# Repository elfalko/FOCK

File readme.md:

# FOCK - Falk's Overstaggered Corne Keyboard

FOCK at work, still waiting for batteries

Underside with simple standoff tenting and battery held by double sided tape

## Status

V2 is my daily driver running on ZMK since 09/22.

There is no firmware supporting the USB-C connection between halves yet, but electronically the connections should be sound.

## Why

[CRKBD](https://github.com/foostan/crkbd) is nice, but could use more stagger, a num row and USB-C

## Features

* fully reversible PCB
* 54 keys (6x4 + 4 thumb keys per side)
* nice!nanoV2 driven, pro-micro compatible
* usb c cable for connection between halves
* battery support
* [ZMK support](https://github.com/elfalko/fock-zmk)

Explicitly not planned:

* LEDs (over/under/any glow)
* return to TRRS
* Rotary encoders

## Repo overview

* Readme - this readme
* fock.yaml - generator file for [ergogen](https://github.com/ergogen/ergogen) (requires [the master branch from my fork](https://github.com/elfalko/ergogen/tree/master) though, since several footprints have been heavily updated)
* img/ - images for documentation
* [Assembly manual](./assembly.md)

## TODO or future plans

* [ ] QMK support
* [ ] optional num row w mouse bites
* [ ] good case
* [ ] trackball/trackpad support

## License and usage

Feel free to use anything in this repo for inspiration and for any projects.
If you do, please send me a message, I will be stoked to hear about it.

Officially, this is under LGPLv2.1 license.

Please be aware that this is a personal project and not subject to any kind of safety testing other than me using it daily and not having electrified myself doing so (yet).
All risks using this are your own.

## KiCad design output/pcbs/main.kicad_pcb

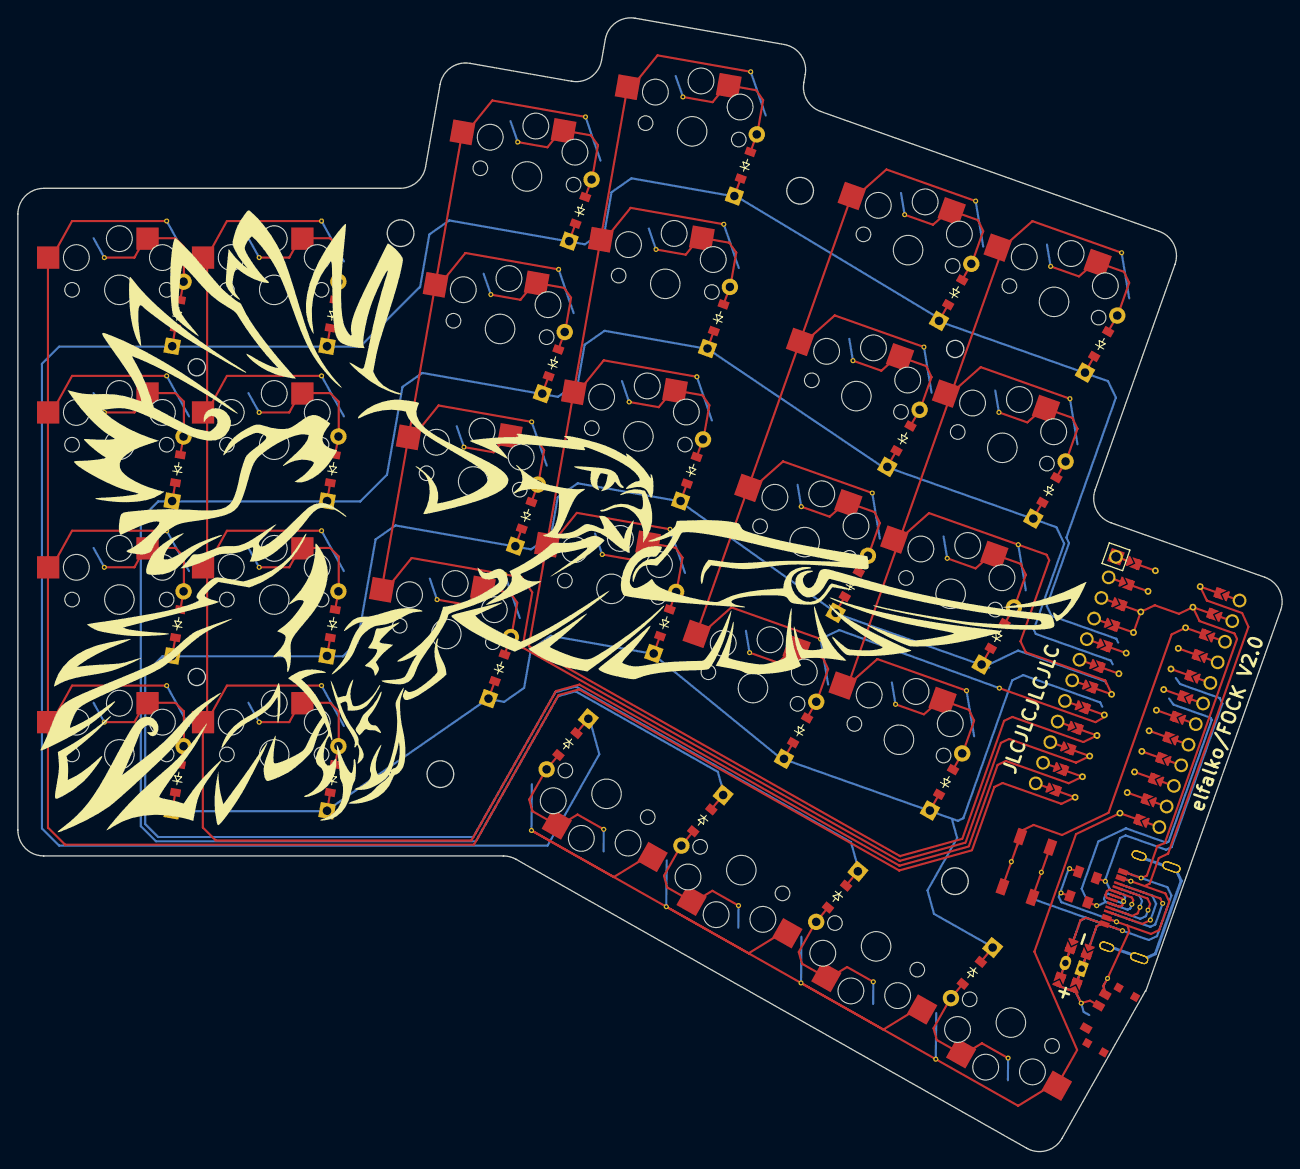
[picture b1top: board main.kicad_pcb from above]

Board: 2 copper layers, 147.0 x 131.8 mm, 71 parts (1 on the bottom side), 52 nets.

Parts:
B1: SW_TACT_ALPS_SKQGABE010
D1, D2, D3, D4, D5, D6, D7, D8, D9, D10, D11, D12, D13, D14, D15, D16, D17, D18, D19, D20, D21, D22, D23, D24, D25, D26, D27, D28: ComboDiode
J1, J2, J3, J4: solderjumper
JST1: JST_PH_S2B-PH-K_02x2.00mm_Angled
MCU1: ProMicro
PAD3, PAD4, PAD5, PAD6: SMDPad
S1, S2, S3, S4, S5, S6, S7, S8, S9, S10, S11, S12, S13, S14, S15, S16, S17, S18, S19, S20, S21, S22, S23, S24, S25, S26, S27, S28: PG1350
T1, T2: SPDT_C128955
USB1, USB2: USB-C-12-Pin-MidMount

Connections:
B1: J1.2, J3.2, JST1.1
B2: J2.2, J4.2, JST1.2
CC1: USB1.B5, USB2.B5
CC2: USB1.A5, USB2.A5
GND: B1.2, J3.1, J4.1, MCU1.2, MCU1.21, MCU1.22, USB1.A1, USB2.A1
P2: MCU1.20, USB1.A7, USB1.B7, USB2.A7, USB2.B7
P3: MCU1.19, USB1.A6, USB1.B6, USB2.A6, USB2.B6
P4: MCU1.18, S21.2, S22.2, S23.2, S24.2
P5: MCU1.17, S17.2, S18.2, S19.2, S20.2
P6: MCU1.16, PAD6.1, S13.2, S14.2, S15.2, S16.2
P7: MCU1.15, PAD5.1, S9.2, S10.2, S11.2, S12.2
P8: MCU1.14, PAD4.1, S5.2, S6.2, S7.2, S8.2
P9: MCU1.13, PAD3.1, S1.2, S2.2, S3.2, S4.2
P10: MCU1.12, S25.2, S26.2, S27.2, S28.2
P18: D1.1, D5.1, D9.1, D13.1, D17.1, D21.1, D25.1, MCU1.8
P19: D2.1, D6.1, D10.1, D14.1, D18.1, D22.1, D26.1, MCU1.7
P20: D3.1, D7.1, D11.1, D15.1, D19.1, D23.1, D27.1, MCU1.6
P21: D4.1, D8.1, D12.1, D16.1, D20.1, D24.1, D28.1, MCU1.5
RAW: MCU1.1, T1.3, T2.1, USB1.A4, USB2.A4
RAWER: J1.1, J2.1, T1.2, T2.2
RST: B1.1, MCU1.3
SBU1: USB1.A8, USB2.A8
SBU2: USB1.B8, USB2.B8
SHIELD: USB1.S1, USB2.S1
index_bottom: D17.2, S17.1
index_home: D18.2, S18.1
index_num: D20.2, S20.1
index_top: D19.2, S19.1
inner_bottom: D21.2, S21.1
inner_home: D22.2, S22.1
inner_num: D24.2, S24.1
inner_top: D23.2, S23.1
middle_bottom: D13.2, S13.1
middle_home: D14.2, S14.1
middle_num: D16.2, S16.1
middle_top: D15.2, S15.1
outer_bottom: D1.2, S1.1
outer_home: D2.2, S2.1
outer_num: D4.2, S4.1
outer_top: D3.2, S3.1
pinky_bottom: D5.2, S5.1
pinky_home: D6.2, S6.1
pinky_num: D8.2, S8.1
pinky_top: D7.2, S7.1
ring_bottom: D9.2, S9.1
ring_home: D10.2, S10.1
ring_num: D12.2, S12.1
ring_top: D11.2, S11.1
thumb_bottom: D25.2, S25.1
thumb_home: D26.2, S26.1
thumb_num: D28.2, S28.1
thumb_top: D27.2, S27.1

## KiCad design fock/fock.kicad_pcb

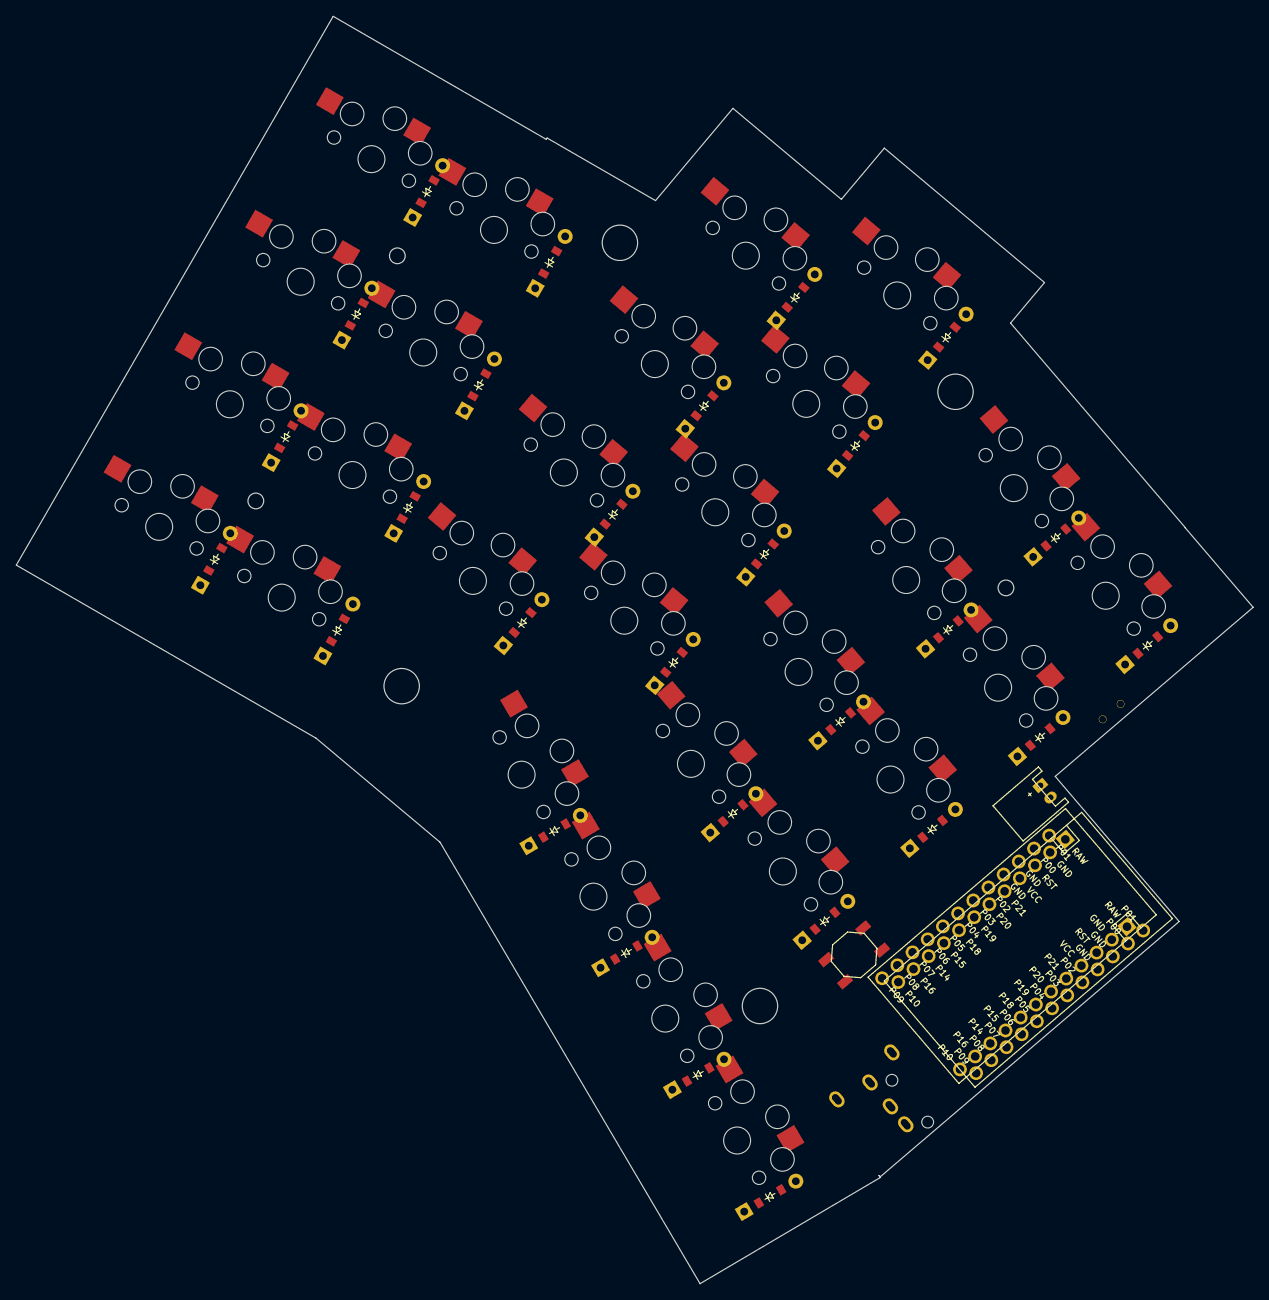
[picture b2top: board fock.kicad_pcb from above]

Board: 2 copper layers, 157.3 x 161.2 mm, 61 parts (0 on the bottom side), 54 nets, no tracks yet.

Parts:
B1: SW_TACT_ALPS_SKQGABE010
D1, D2, D3, D4, D5, D6, D7, D8, D9, D10, D11, D12, D13, D14, D15, D16, D17, D18, D19, D20, D21, D22, D23, D24, D25, D26, D27, D28: ComboDiode
JST1: JST_PH_S2B-PH-K_02x2.00mm_Angled
MCU1, MCU2: ProMicro
S1, S2, S3, S4, S5, S6, S7, S8, S9, S10, S11, S12, S13, S14, S15, S16, S17, S18, S19, S20, S21, S22, S23, S24, S25, S26, S27, S28: PG1350
T1: SPDT_C128955

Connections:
GND: B1.2, JST1.2, MCU1.2, MCU1.15, MCU1.16, MCU2.2, MCU2.15, MCU2.16
P0: MCU1.14, MCU2.14
P1: MCU1.13, MCU2.13, S1.2, S2.2, S3.2, S4.2
P2: MCU1.17, MCU2.17, S5.2, S6.2, S7.2, S8.2
P3: MCU1.18, MCU2.18, S9.2, S10.2, S11.2, S12.2
P4: MCU1.19, MCU2.19, S13.2, S14.2, S15.2, S16.2
P5: MCU1.20, MCU2.20, S17.2, S18.2, S19.2, S20.2
P6: MCU1.21, MCU2.21, S21.2, S22.2, S23.2, S24.2
P7: MCU1.22, MCU2.22, S25.2, S26.2, S27.2, S28.2
P8: MCU1.23, MCU2.23
P9: MCU1.24, MCU2.24
P10: D1.1, D1.2, D5.1, D5.2, D9.1, D9.2, D13.1, D13.2, D17.1, D17.2, D21.1, D21.2, D25.1, D25.2, MCU1.12, MCU2.12
P11: D2.1, D2.2, D6.1, D6.2, D10.1, D10.2, D14.1, D14.2, D18.1, D18.2, D22.1, D22.2, D26.1, D26.2
P12: D3.1, D3.2, D7.1, D7.2, D11.1, D11.2, D15.1, D15.2, D19.1, D19.2, D23.1, D23.2, D27.1, D27.2
P13: D4.1, D4.2, D8.1, D8.2, D12.1, D12.2, D16.1, D16.2, D20.1, D20.2, D24.1, D24.2, D28.1, D28.2
P14: MCU1.10, MCU2.10
P15: MCU1.9, MCU2.9
P16: MCU1.11, MCU2.11
P18: MCU1.8, MCU2.8
P19: MCU1.7, MCU2.7
P20: MCU1.6, MCU2.6
P21: MCU1.5, MCU2.5
RAW: MCU1.1, MCU2.1, T1.1
RAWER: JST1.1, T1.2
RST: B1.1, MCU1.3, MCU2.3
VCC: MCU1.4, MCU2.4
index_bottom: D17.1, D17.2, S17.1
index_home: D18.1, D18.2, S18.1
index_num: D20.1, D20.2, S20.1
index_top: D19.1, D19.2, S19.1
inner_bottom: D21.1, D21.2, S21.1
inner_home: D22.1, D22.2, S22.1
inner_num: D24.1, D24.2, S24.1
inner_top: D23.1, D23.2, S23.1
middle_bottom: D13.1, D13.2, S13.1
middle_home: D14.1, D14.2, S14.1
middle_num: D16.1, D16.2, S16.1
middle_top: D15.1, D15.2, S15.1
outer_bottom: D1.1, D1.2, S1.1
outer_home: D2.1, D2.2, S2.1
outer_num: D4.1, D4.2, S4.1
outer_top: D3.1, D3.2, S3.1
pinky_bottom: D5.1, D5.2, S5.1
pinky_home: D6.1, D6.2, S6.1
pinky_num: D8.1, D8.2, S8.1
pinky_top: D7.1, D7.2, S7.1
ring_bottom: D9.1, D9.2, S9.1
ring_home: D10.1, D10.2, S10.1
ring_num: D12.1, D12.2, S12.1
ring_top: D11.1, D11.2, S11.1
thumb_bottom: D25.1, D25.2, S25.1
thumb_home: D26.1, D26.2, S26.1
thumb_num: D28.1, D28.2, S28.1
thumb_top: D27.1, D27.2, S27.1

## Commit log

2022-05-01 moved initial files to main branch
2022-05-01 updated readme with pic
2022-05-01 added cache.works link in again
2022-05-01 fixed crkbd link
2022-05-01 updated readme with info
2022-06-27 added num row and proper stl for handwiring
2022-07-24 first pcb version
2022-07-30 massively updated pcb
    * moved index row a bit to avoid overlaps
    * removed mirror in favor of mirrored part footprints
    * added trrs, switches, mounting holes
2022-08-02 added some links
2022-08-06 added schematics and footprints from ai03 guide
2022-08-06 removes kicad stuff
2022-08-06 last version before switching to local ergogen build
2022-08-06 link to great keeb building guide
2022-08-06 changed to new footprints
2022-08-06 3/4 normal pcb with fillet
2022-08-06 sick filleted outline
2022-08-06 fixed the remaining fillet issue
2022-08-07 updated design
2022-08-07 first full routing
2022-08-07 more updates with feedback from initial routing
2022-08-07 more todos for next version
2022-08-07 routing for V1.0 with logo and text
2022-08-27 to zip stuff for manufacture
2022-08-27 severely updated to include prerouted key groups
    saves around 14 connections per switch
2022-08-27 fixed radius diameter error in some holes
2022-08-27 overlap between diode and pads between middle and ring finger
2022-08-27 improved row connections
2022-08-27 moved usbc to anchor point and build half a flip connector
2022-08-28 fixed weird bug and finished usbc v1.0
2022-08-28 compactified usb c footprint
2022-08-28 before usbc anchor rework
2022-08-28 layout improved
    thumb cluster connected
    changed to flippable reset switch
    cut off key outcrop for usbc
    way more connections, mostly collected towards mcu
2022-08-28 i2c connections, pullups and mcu connections
2022-08-31 shifted pinky and index col trace to avoid hole
2022-08-31 smaller pads
2022-08-31 battery and reset switch
2022-08-31 improved wiring
2022-09-01 adds logo
2022-09-02 all connections
2022-09-02 labels
2022-09-02 V2 production ready
2022-09-02 updated images
2022-09-02 update link to ergogen fork
2022-09-02 readmeupdate
2022-09-03 moved makefile
2022-09-03 better styling attempt
2022-09-03 better routing to fix warnings
2022-10-09 update docu
2022-10-09 V2 footprint kicad
2022-10-11 updated ergogen fork link
2022-12-04 update readme and add assembly manual
2022-12-04 adds underside image an minimal formatting
2023-05-08 adds cases for modelling
2023-05-08 pcb model now has underside spacers for parts
2023-05-08 better pcb stl and a foot
2023-05-09 more stand options
